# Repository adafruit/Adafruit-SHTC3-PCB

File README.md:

## Adafruit Sensirion SHTC3T Temperature & Humidity Sensor PCB

<a href="http://www.adafruit.com/products/4636"><br/>
Click here to purchase one from the Adafruit shop</a>

PCB files for the Adafruit Sensirion SHTC3T Temperature & Humidity Sensor. 

Format is EagleCAD schematic and board layout
* https://www.adafruit.com/product/4636

### Description

Sensirion Temperature/Humidity sensors are some of the finest & highest-accuracy devices you can get. And with a true I2C interface, reading the data is for easy. The SHTC3 sensor has an excellent ±2% relative humidity and ±0.2°C accuracy for most uses.

Unlike some earlier SHT sensors, this sensor has a true I2C interface for easy interfacing with only two wires (plus power and ground!). Thanks to the voltage regulator and level shifting circuitry we've included on the breakout It is also is 3V or 5V compliant, so you can power and communicate with it using any microcontroller or microcomputer.

Such a lovely chip - so we spun up a breakout board with the SHTC3 and some supporting circuitry such as pullup resistors and capacitors. To make things even easier, we've included SparkFun Qwiic compatible STEMMA QT connectors for the I2C bus so you don't even need to solder! If you prefer working on a breadboard, each order comes with one fully assembled and tested PCB breakout and a small piece of header. You'll need to solder the header onto the PCB but it's fairly easy and takes only a few minutes even for a beginner.

### License

Adafruit invests time and resources providing this open source design, please support Adafruit and open-source hardware by purchasing products from [Adafruit](https://www.adafruit.com)!

Designed by Limor Fried/Ladyada for Adafruit Industries.

Creative Commons Attribution/Share-Alike, all text above must be included in any redistribution. 
See license.txt for additional details.

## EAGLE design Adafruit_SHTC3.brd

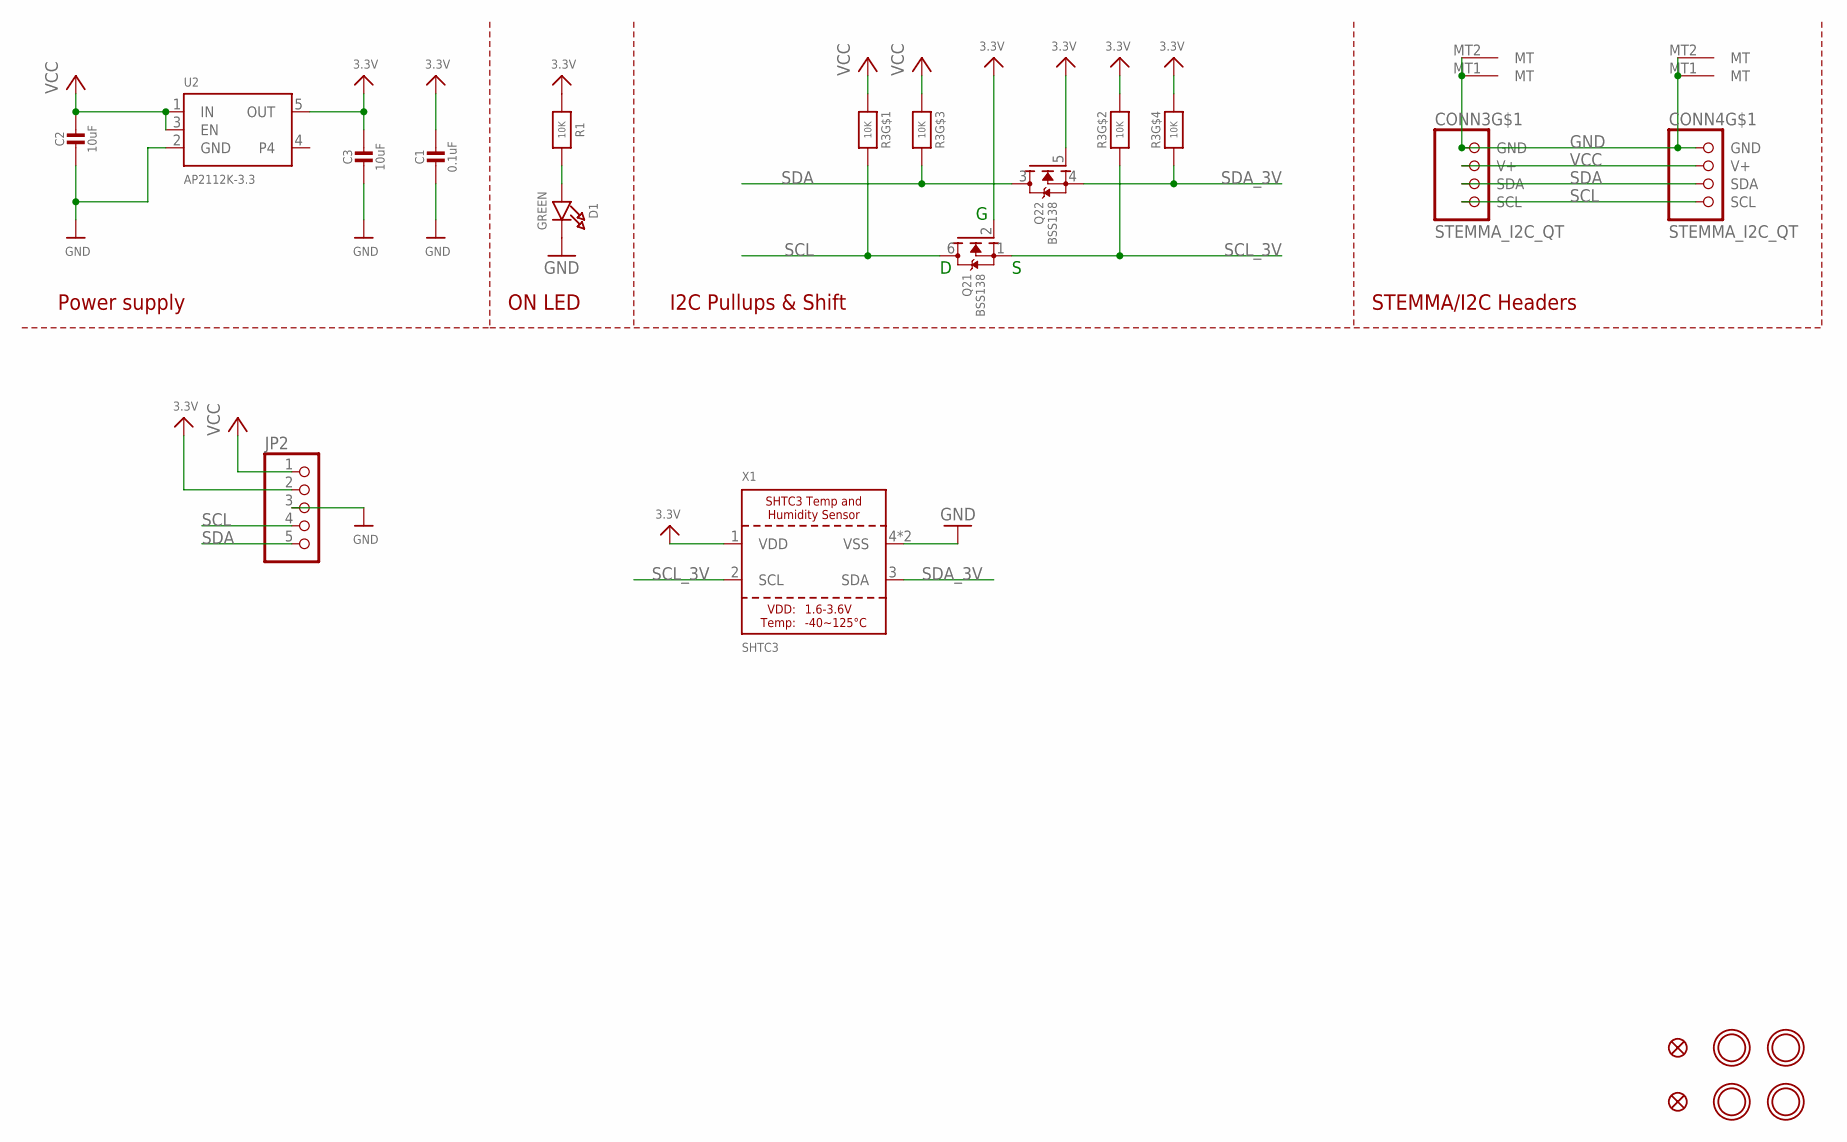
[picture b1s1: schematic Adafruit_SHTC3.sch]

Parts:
C1: 0.1uF; 0603-NO
C2, C3: 10uF; 0805-NO
CONN3, CONN4: STEMMA_I2C_QT; JST_SH4
D1: GREEN; CHIPLED_0603_NOOUTLINE
FID3, FID4: FIDUCIAL_1MM
JP2: HEADER-1X570MIL; 1X05_ROUND_70
Q2: BSS138; SOT363
R1: 10K; 0603-NO
R3: 10K; RESPACK_4X0603
U2: AP2112K-3.3; SOT23-5
U$1, U$17, U$19, U$21: MOUNTINGHOLE2.5; MOUNTINGHOLE_2.5_PLATED
X1: SHTC3

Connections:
3.3V: C1.1, C3.1, JP2.2, Q2.2 (G), Q2.5 (G), R1.1, R3.2 (1), R3.4 (1), U2.5 (OUT), X1.1 (VDD)
GND: C1.2, C2.2, C3.2, CONN3.1 (GND), CONN3.MT1 (MT), CONN3.MT2 (MT), CONN4.1 (GND), CONN4.MT1 (MT), CONN4.MT2 (MT), D1.C, JP2.3, U2.2 (GND), X1.4 (VSS), X1.MNT (VSS)
unnamed: D1.A, R1.2
SCL: CONN3.4 (SCL), CONN4.4 (SCL), JP2.4, Q2.6 (D), R3.8 (2)
SCL_3V: Q2.1 (S), R3.7 (2), X1.2 (SCL)
SDA: CONN3.3 (SDA), CONN4.3 (SDA), JP2.5, Q2.3 (D), R3.6 (2)
SDA_3V: Q2.4 (S), R3.5 (2), X1.3 (SDA)
VCC: C2.1, CONN3.2 (V+), CONN4.2 (V+), JP2.1, R3.1, R3.3 (1), U2.1 (IN), U2.3 (EN)

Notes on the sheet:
I2C Pullups & Shift
STEMMA/I2C Headers
ON LED
Power supply

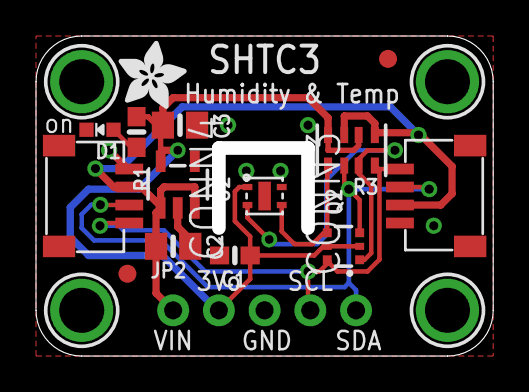
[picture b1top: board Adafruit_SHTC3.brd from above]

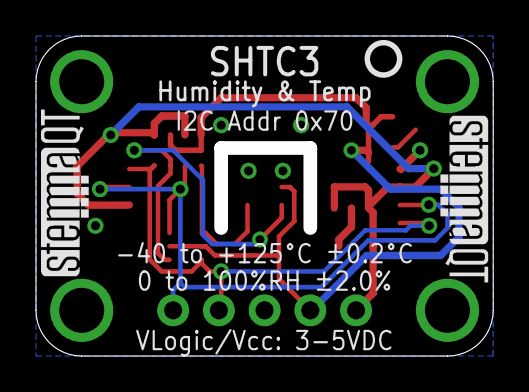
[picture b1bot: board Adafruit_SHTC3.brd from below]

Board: 2 copper layers, 24.6 x 17.0 mm, 22 parts (3 on the bottom side), 8 nets.

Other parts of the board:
U$22: ADAFRUIT_3.5MM
U$25: PCBFEAT-REV-040
U$30, U$31: STEMMAQT

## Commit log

2020-06-16 initial commit with Rev A

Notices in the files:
parts and their libraries:
microbuilder: This work is placed in the public domain, and may be freely used for commercial and non-commercial work with the following conditions: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
